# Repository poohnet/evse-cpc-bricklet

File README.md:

# evse-cpc-bricklet
CP Disconnect for WARP on Steroids

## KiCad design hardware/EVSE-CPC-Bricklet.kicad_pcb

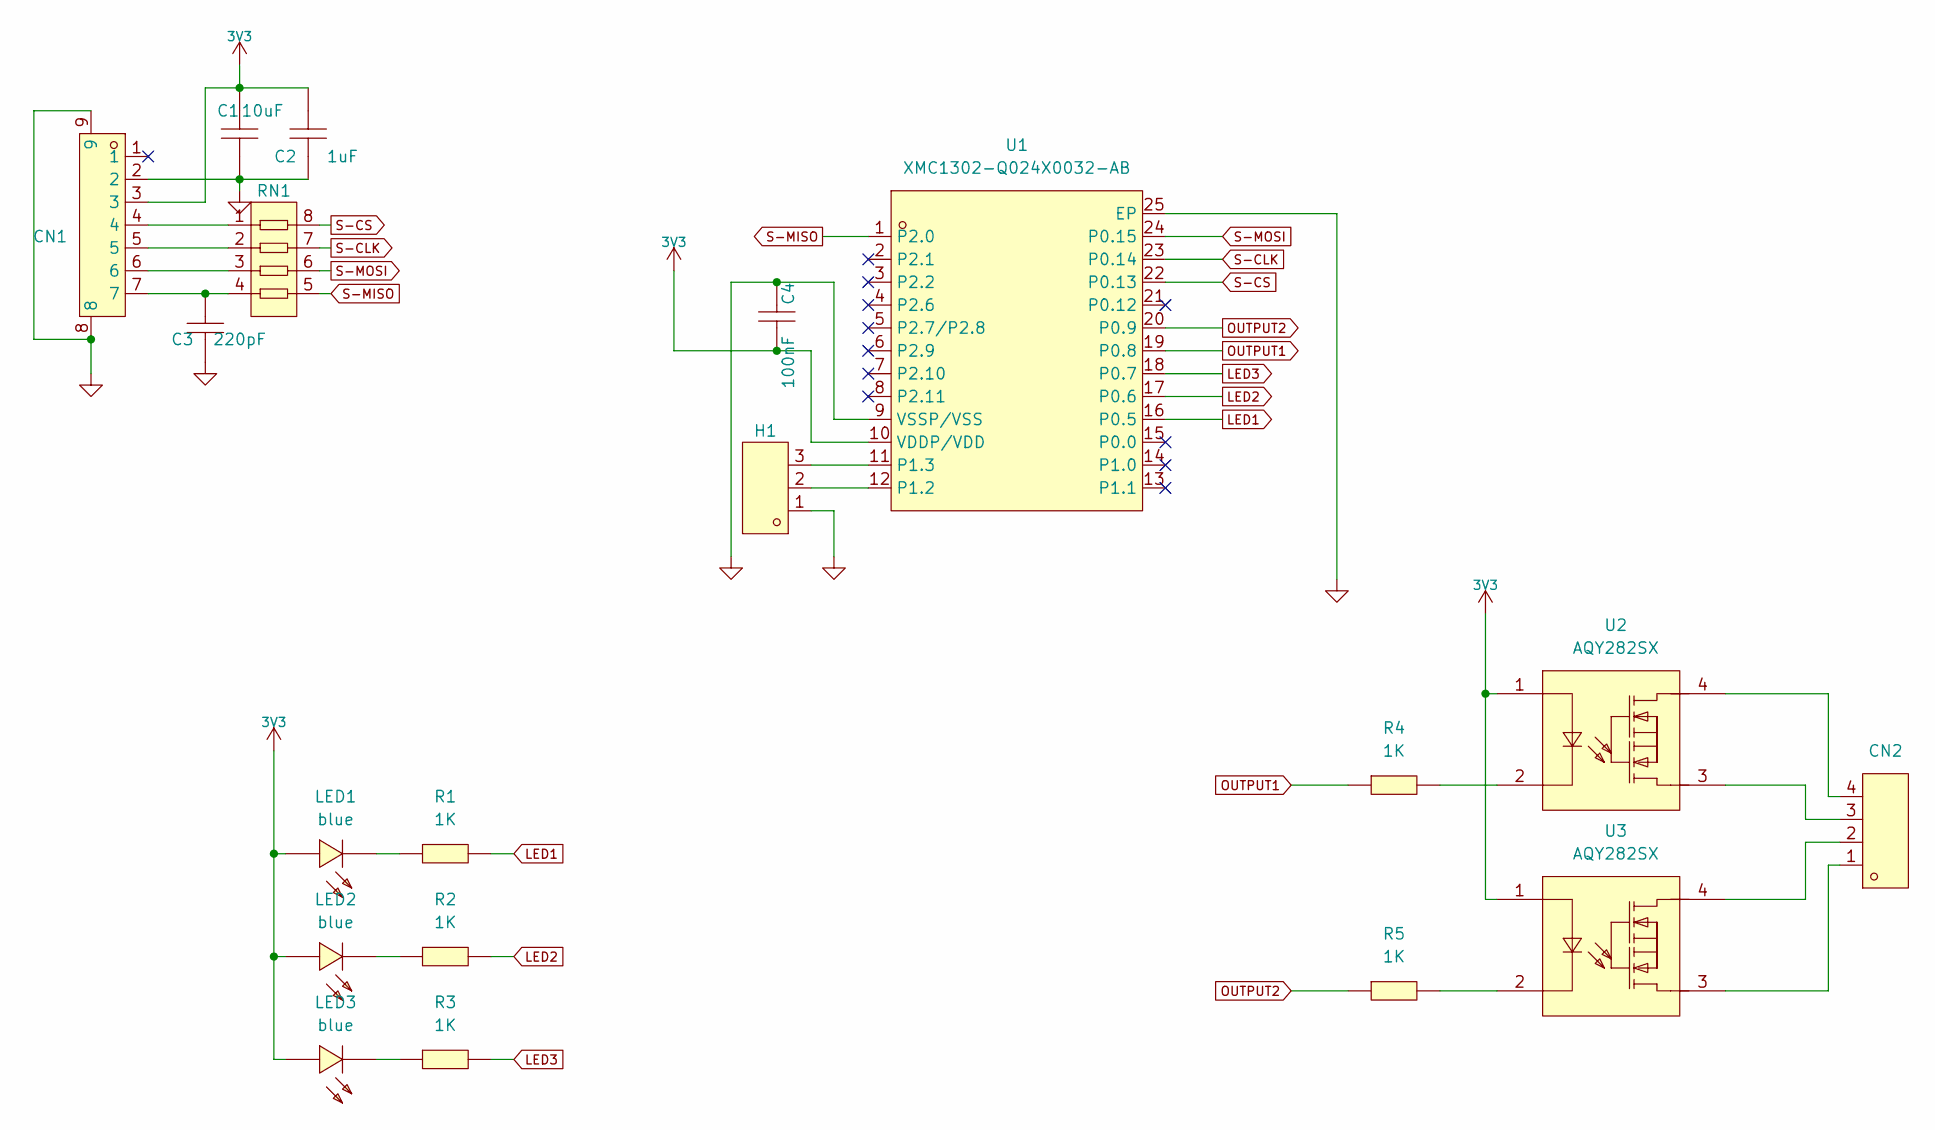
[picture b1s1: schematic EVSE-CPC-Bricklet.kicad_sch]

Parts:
C1: 10uF; C0805; LCSC Part C1222438
C2: 1uF; C0603; LCSC Part C513775
C3: 220pF; C0402; LCSC Part C107025
C4: 100nF; C0603; LCSC Part C30926
CN1: HC-GH-7PWTKK; CONN-SMD_7P-P1.25_HCTL_HC-GH-7PWTKK; LCSC Part C3011949
CN2: DB2ERC-3.81-4P; CONN-TH_4P-P3.81_DB2ERC-3.81-4P; LCSC Part C395698
H1: X1311WV-03J-C18D27; HDR-TH_3P-P1.27-V-M; LCSC Part C2881648
LED1, LED2, LED3: blue; LED0603-RD; LCSC Part C84266
R1, R2, R3, R4, R5: 1K; R0603; LCSC Part C22548
RN1: CRA034RJ82RP05; RES-ARRAY-SMD_0603-8P-L3.2-W1.6-BL; LCSC Part C429276
U1: XMC1302-Q024X0032-AB; VQFN-24_L4.0-W4.0-P0.50-TL-EP2.7; LCSC Part C5121285
U2, U3: AQY282SX; SOP-4_L4.3-W4.4-P2.54-LS7.0-BL; LCSC Part C250827

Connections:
3V3: C1.1, C2.1, C4.2, CN1.3, LED1.2 (+), LED2.2 (+), LED3.2 (+), U1.10 (VDDP/VDD), U2.1, U3.1
GND: C1.2, C2.2, C3.2, C4.1, CN1.2, CN1.8, CN1.9, H1.1, U1.9 (VSSP/VSS), U1.25 (EP)
LED1: R1.2, U1.16 (P0.5)
LED2: R2.2, U1.17 (P0.6)
LED3: R3.2, U1.18 (P0.7)
unnamed: C3.1, CN1.7, RN1.4
unnamed: CN1.4, RN1.1
unnamed: CN1.5, RN1.2
unnamed: CN1.6, RN1.3
unnamed: CN2.1, U3.3
unnamed: CN2.2, U3.4
unnamed: CN2.3, U2.3
unnamed: CN2.4, U2.4
unnamed: LED1.1 (-), R1.1
unnamed: LED2.1 (-), R2.1
unnamed: LED3.1 (-), R3.1
unnamed: R4.2, U2.2
unnamed: R5.2, U3.2
unnamed: H1.2, U1.12 (P1.2)
unnamed: H1.3, U1.11 (P1.3)
OUTPUT1: R4.1, U1.19 (P0.8)
OUTPUT2: R5.1, U1.20 (P0.9)
S-CLK: RN1.7, U1.23 (P0.14)
S-CS: RN1.8, U1.22 (P0.13)
S-MISO: RN1.5, U1.1 (P2.0)
S-MOSI: RN1.6, U1.24 (P0.15)

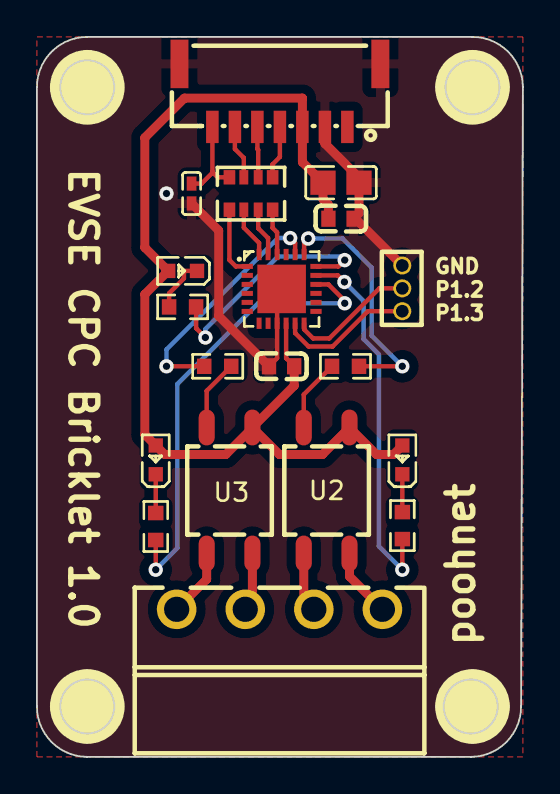
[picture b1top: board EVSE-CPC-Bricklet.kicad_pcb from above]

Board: 2 copper layers, 27.0 x 40.0 mm, 20 parts (1 on the bottom side), 26 nets.

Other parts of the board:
VAL: WEEE_7mm

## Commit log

2024-01-18 Add initial files and directories
2024-01-18 Add KiCad and JLCPCB production files
2024-01-19 Relay configuration
2024-01-24 fix relay configuration
